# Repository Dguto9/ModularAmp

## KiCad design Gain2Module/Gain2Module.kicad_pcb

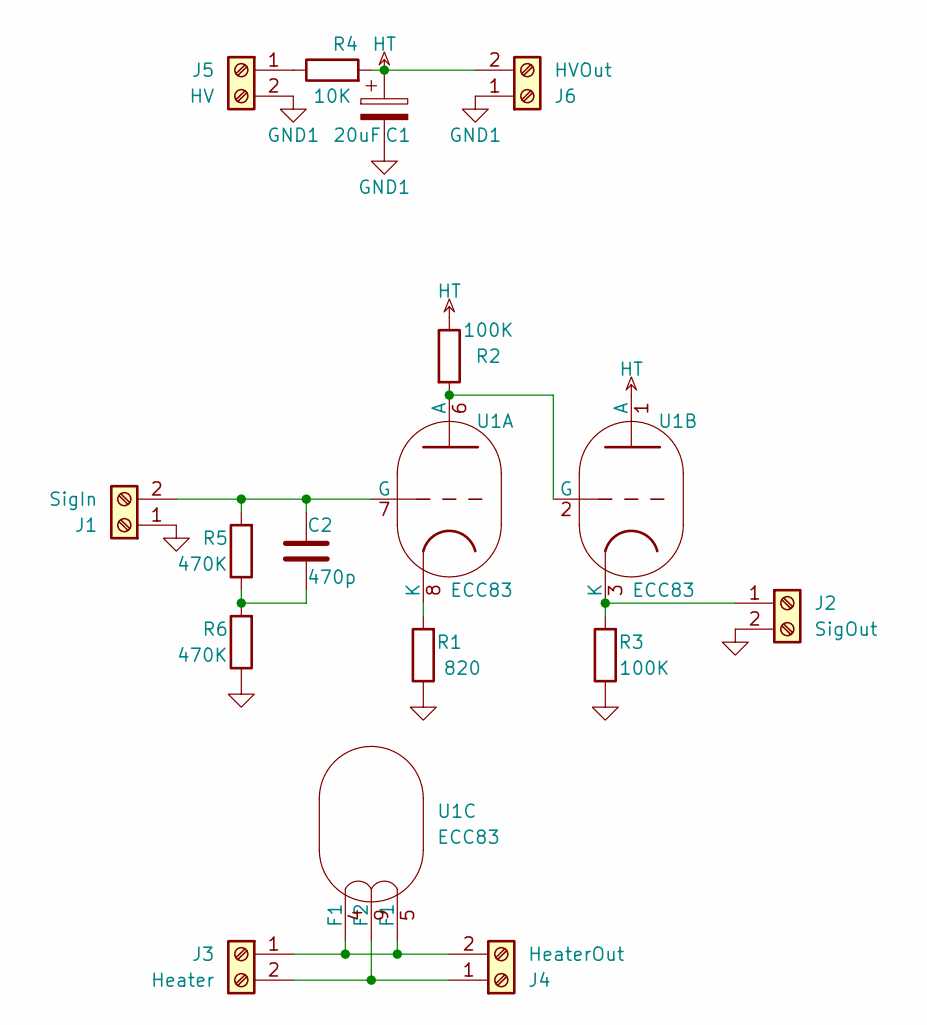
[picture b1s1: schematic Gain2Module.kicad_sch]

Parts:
C1: 20uF; CP_Radial_D13.0mm_P5.00mm
C2: 470p; FG26 Cap
J1: SigIn; Molex_Micro-Fit_3.0_43650-0200_1x02_P3.00mm_Horizontal
J2: SigOut; Molex_Micro-Fit_3.0_43650-0200_1x02_P3.00mm_Horizontal
J3: Heater; Molex_Micro-Fit_3.0_43650-0215_1x02_P3.00mm_Vertical
J4: HeaterOut; Molex_Micro-Fit_3.0_43650-0215_1x02_P3.00mm_Vertical
J5: HV; Molex_Micro-Fit_3.0_43650-0200_1x02_P3.00mm_Horizontal
J6: HVOut; Molex_Micro-Fit_3.0_43650-0200_1x02_P3.00mm_Horizontal
R1: 820; R_Axial_DIN0309_L9.0mm_D3.2mm_P12.70mm_Horizontal
R2, R3: 100K; R_Axial_DIN0309_L9.0mm_D3.2mm_P12.70mm_Horizontal
R4: 10K; R_Axial_DIN0309_L9.0mm_D3.2mm_P12.70mm_Horizontal
R5, R6: 470K; R_Axial_DIN0309_L9.0mm_D3.2mm_P12.70mm_Horizontal
U1: ECC83; BELTON_VT9-PT

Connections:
GND: J1.1, J2.2, R1.1, R3.1, R6.1
GND1: C1.2, J5.2, J6.1
HT: C1.1, J6.2, R2.1, R4.2, U1.1 (A)
unnamed: C2.2, R5.1, R6.2
unnamed: C2.1, J1.2, R5.2, U1.7 (G)
unnamed: J2.1, R3.2, U1.3 (K)
unnamed: J3.1, J4.2, U1.4 (F1), U1.5 (F1)
unnamed: J3.2, J4.1, U1.9 (F2)
unnamed: J5.1, R4.1
unnamed: R2.2, U1.2 (G), U1.6 (A)
unnamed: R1.2, U1.8 (K)

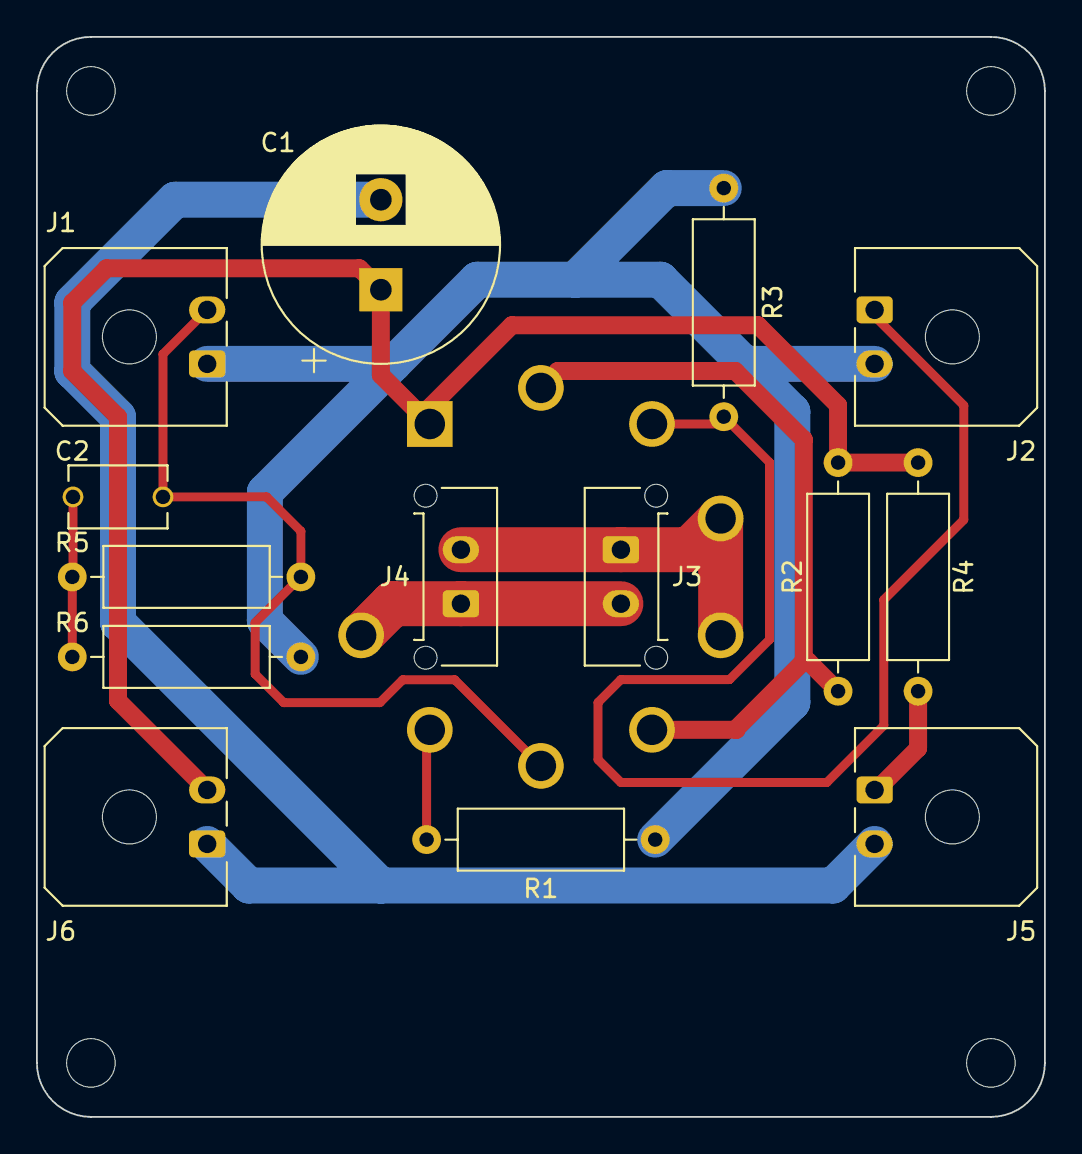
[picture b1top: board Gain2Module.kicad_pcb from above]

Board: 2 copper layers, 56.0 x 60.0 mm, 15 parts (1 on the bottom side), 11 nets.

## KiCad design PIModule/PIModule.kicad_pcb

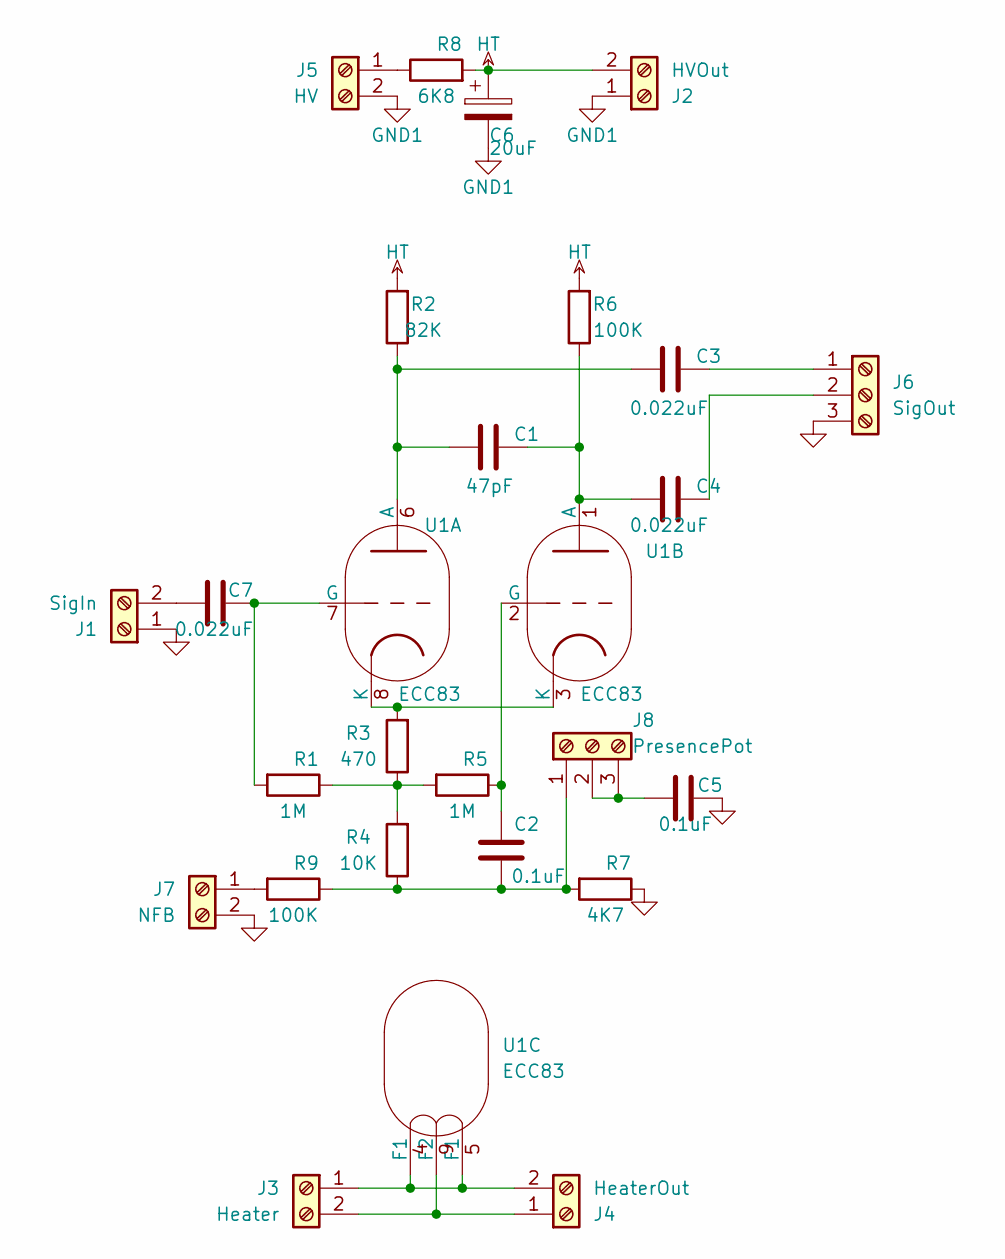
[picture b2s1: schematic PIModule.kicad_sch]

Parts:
C1: 47pF; FG26 Cap
C2, C5: 0.1uF; FG26 Cap
C3, C4, C7: 0.022uF; C_Rect_L13.0mm_W4.0mm_P10.00mm_FKS3_FKP3_MKS4
C6: 20uF; CP_Radial_D13.0mm_P5.00mm
J1: SigIn; Molex_Micro-Fit_3.0_43650-0200_1x02_P3.00mm_Horizontal
J2: HVOut; Molex_Micro-Fit_3.0_43650-0200_1x02_P3.00mm_Horizontal
J3: Heater; Molex_Micro-Fit_3.0_43650-0215_1x02_P3.00mm_Vertical
J4: HeaterOut; Molex_Micro-Fit_3.0_43650-0215_1x02_P3.00mm_Vertical
J5: HV; Molex_Micro-Fit_3.0_43650-0200_1x02_P3.00mm_Horizontal
J6: SigOut; Molex_Micro-Fit_3.0_43650-0300_1x03_P3.00mm_Horizontal
J7: NFB; Molex_Micro-Fit_3.0_43650-0215_1x02_P3.00mm_Vertical
J8: PresencePot; Molex_Micro-Fit_3.0_43650-0315_1x03_P3.00mm_Vertical
R1, R5: 1M; R_Axial_DIN0309_L9.0mm_D3.2mm_P12.70mm_Horizontal
R2: 82K; R_Axial_DIN0309_L9.0mm_D3.2mm_P12.70mm_Horizontal
R3: 470; R_Axial_DIN0309_L9.0mm_D3.2mm_P12.70mm_Horizontal
R4: 10K; R_Axial_DIN0309_L9.0mm_D3.2mm_P12.70mm_Horizontal
R6, R9: 100K; R_Axial_DIN0309_L9.0mm_D3.2mm_P12.70mm_Horizontal
R7: 4K7; R_Axial_DIN0309_L9.0mm_D3.2mm_P12.70mm_Horizontal
R8: 6K8; R_Axial_DIN0309_L9.0mm_D3.2mm_P12.70mm_Horizontal
U1: ECC83; BELTON_VT9-PT

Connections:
GND: C5.1, J1.1, J6.3, J7.2, R7.1
GND1: C6.2, J2.1, J5.2
HT: C6.1, J2.2, R2.2, R6.2, R8.2
unnamed: C7.1, J1.2
unnamed: J3.1, J4.2, U1.4 (F1), U1.5 (F1)
unnamed: J3.2, J4.1, U1.9 (F2)
unnamed: J5.1, R8.1
unnamed: C3.2, J6.1
unnamed: C4.2, J6.2
unnamed: J7.1, R9.2
unnamed: C2.1, J8.1, R4.1, R7.2, R9.1
unnamed: C5.2, J8.2, J8.3
unnamed: R1.1, R3.1, R4.2, R5.2
unnamed: C1.1, C3.1, R2.1, U1.6 (A)
unnamed: C7.2, R1.2, U1.7 (G)
unnamed: R3.2, U1.3 (K), U1.8 (K)
unnamed: C1.2, C4.1, R6.1, U1.1 (A)
unnamed: C2.2, R5.1, U1.2 (G)

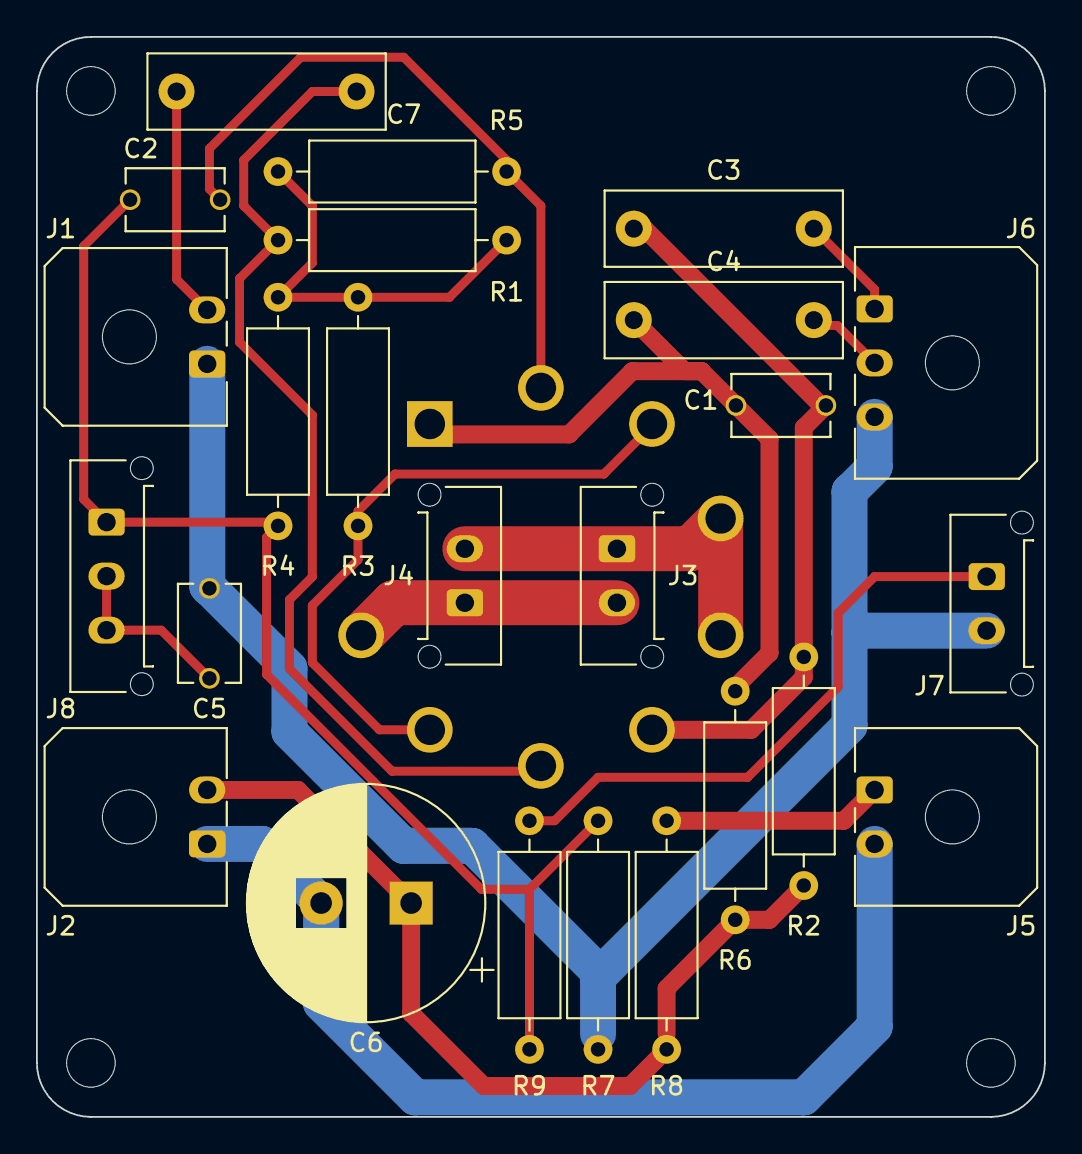
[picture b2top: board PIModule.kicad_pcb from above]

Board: 2 copper layers, 56.0 x 60.0 mm, 25 parts (1 on the bottom side), 18 nets.

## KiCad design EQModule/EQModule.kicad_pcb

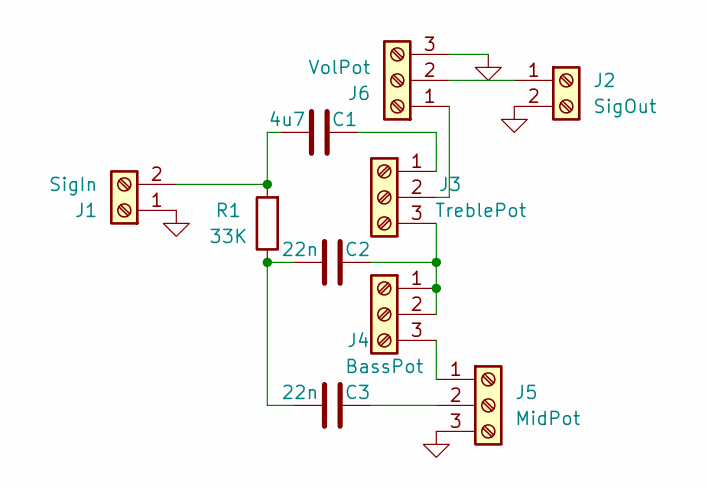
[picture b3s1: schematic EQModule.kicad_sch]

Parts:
C1: 4u7; FG26 Cap
C2, C3: 22n; FG26 Cap
J1: SigIn; Molex_Micro-Fit_3.0_43650-0200_1x02_P3.00mm_Horizontal
J2: SigOut; Molex_Micro-Fit_3.0_43650-0200_1x02_P3.00mm_Horizontal
J3: TreblePot; Molex_Micro-Fit_3.0_43650-0315_1x03_P3.00mm_Vertical
J4: BassPot; Molex_Micro-Fit_3.0_43650-0315_1x03_P3.00mm_Vertical
J5: MidPot; Molex_Micro-Fit_3.0_43650-0315_1x03_P3.00mm_Vertical
J6: VolPot; Molex_Micro-Fit_3.0_43650-0315_1x03_P3.00mm_Vertical
R1: 33K; R_Axial_DIN0309_L9.0mm_D3.2mm_P12.70mm_Horizontal

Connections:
GND: J1.1, J2.2, J5.3, J6.3
unnamed: C2.1, C3.1, R1.1
unnamed: C1.1, J1.2, R1.2
unnamed: J2.1, J6.2
unnamed: C1.2, J3.1
unnamed: J3.2, J6.1
unnamed: C2.2, J3.3, J4.1, J4.2
unnamed: J4.3, J5.1
unnamed: C3.2, J5.2

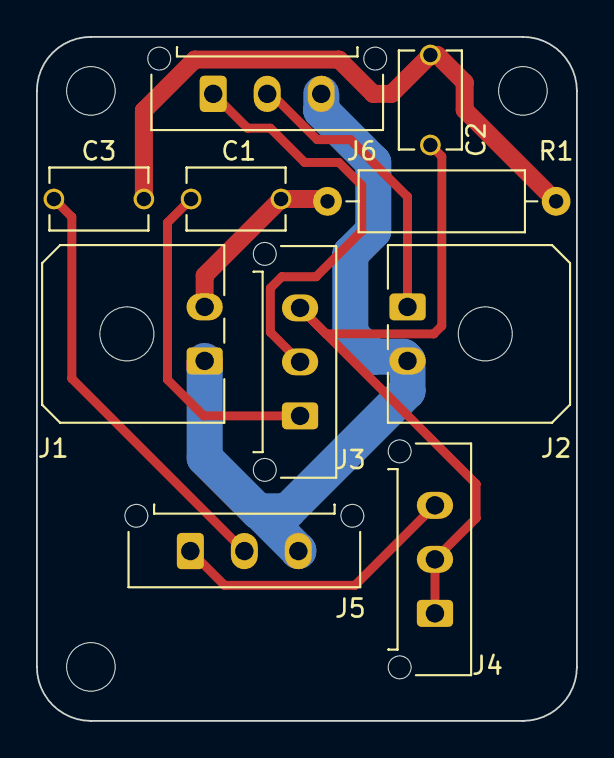
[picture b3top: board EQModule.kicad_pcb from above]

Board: 2 copper layers, 30.0 x 38.0 mm, 10 parts (0 on the bottom side), 9 nets.

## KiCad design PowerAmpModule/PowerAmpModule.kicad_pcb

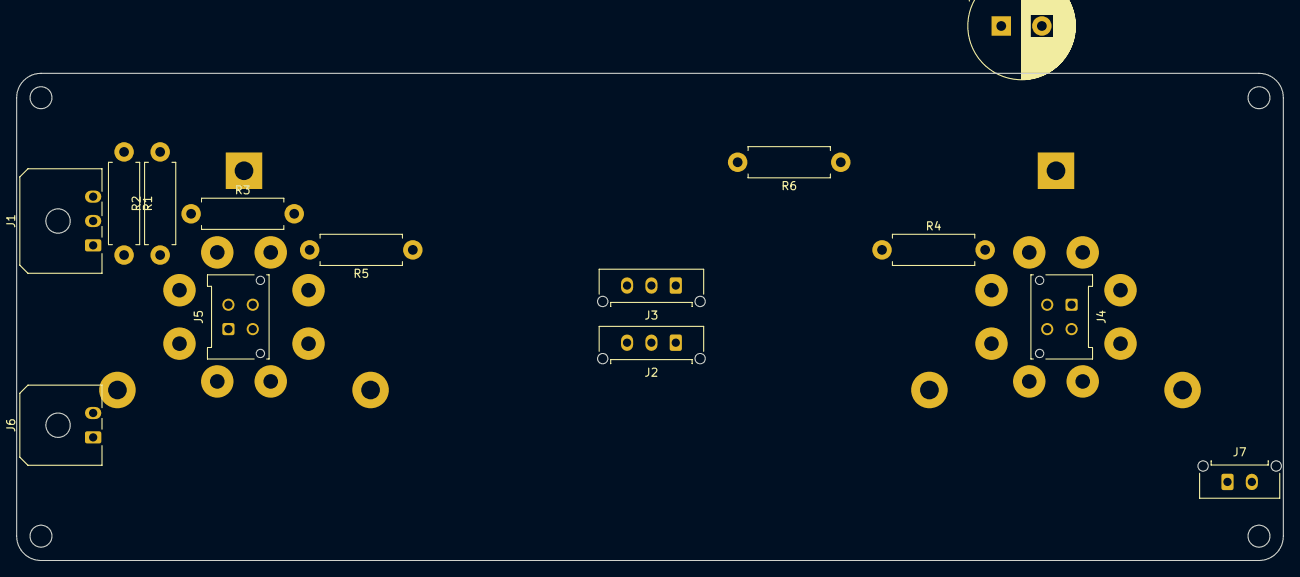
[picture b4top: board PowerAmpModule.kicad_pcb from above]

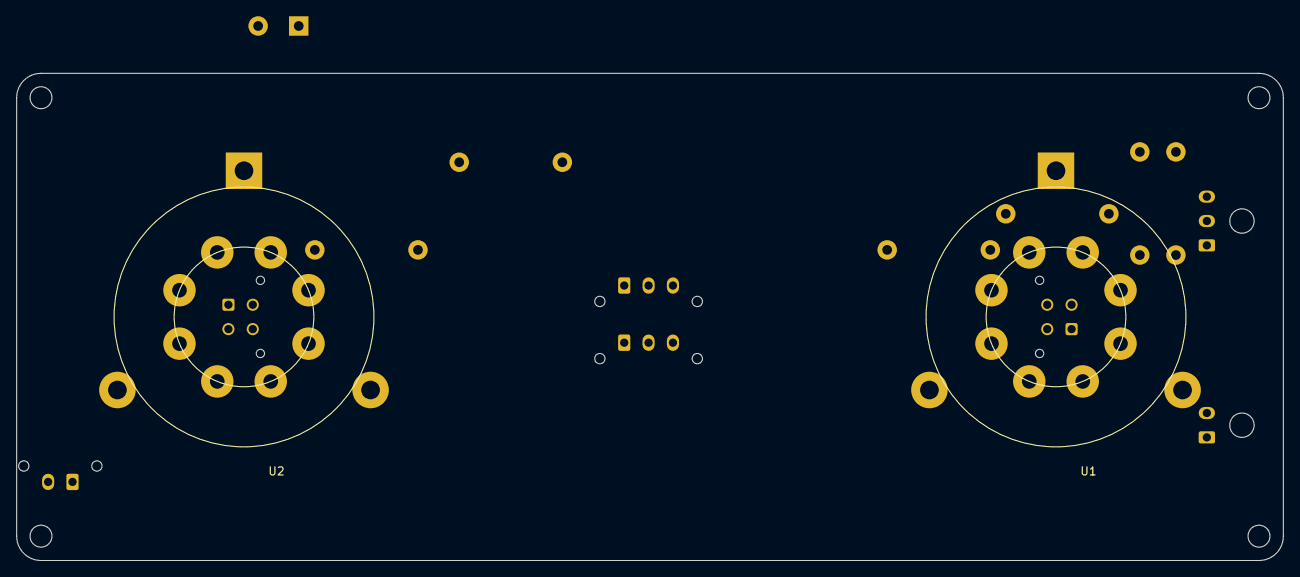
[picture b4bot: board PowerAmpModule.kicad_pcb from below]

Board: 2 copper layers, 156.0 x 60.0 mm, 16 parts (2 on the bottom side), 14 nets, no tracks yet.

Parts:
C1: 20uF; CP_Radial_D13.0mm_P5.00mm
J1: Signal; Molex_Micro-Fit_3.0_43650-0300_1x03_P3.00mm_Horizontal
J2: Power; Molex_Micro-Fit_3.0_43650-0315_1x03_P3.00mm_Vertical
J3: SignalOut; Molex_Micro-Fit_3.0_43650-0315_1x03_P3.00mm_Vertical
J4: Heater; Molex_Micro-Fit_3.0_43045-0412_2x02_P3.00mm_Vertical
J5: HeaterOut; Molex_Micro-Fit_3.0_43045-0412_2x02_P3.00mm_Vertical
J6: PowerOut; Molex_Micro-Fit_3.0_43650-0200_1x02_P3.00mm_Horizontal
J7: Inductor; Molex_Micro-Fit_3.0_43650-0215_1x02_P3.00mm_Vertical
R1, R2: 220K; R_Axial_DIN0411_L9.9mm_D3.6mm_P12.70mm_Horizontal
R3, R4: 5K6; R_Axial_DIN0411_L9.9mm_D3.6mm_P12.70mm_Horizontal
R5, R6: 1K5; R_Axial_DIN0411_L9.9mm_D3.6mm_P12.70mm_Horizontal
U1, U2: 6V6; BELTON_VT8-PTL-01

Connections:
/Bias: J2.2, R1.1, R2.2
GND: C1.2, J1.1, U1.1 (G3), U1.8 (F1), U2.1 (G3), U2.8 (F1)
GND1: J2.3, J6.2
HT: C1.1, J2.1, J3.2, J6.1, J7.1, J7.2, R5.1, R6.1
unnamed: J1.2, R2.1, R4.1
unnamed: J1.3, R1.2, R3.1
unnamed: J3.1, U1.3 (A)
unnamed: J3.3, U2.3 (A)
unnamed: J4.1, J5.1, U1.2 (F1), U2.2 (F1)
unnamed: J4.2, J5.2, U1.7 (F2), U2.7 (F2)
unnamed: R3.2, U1.5 (G1)
unnamed: R5.2, U1.4 (G2)
unnamed: R4.2, U2.5 (G1)
unnamed: R6.2, U2.4 (G2)

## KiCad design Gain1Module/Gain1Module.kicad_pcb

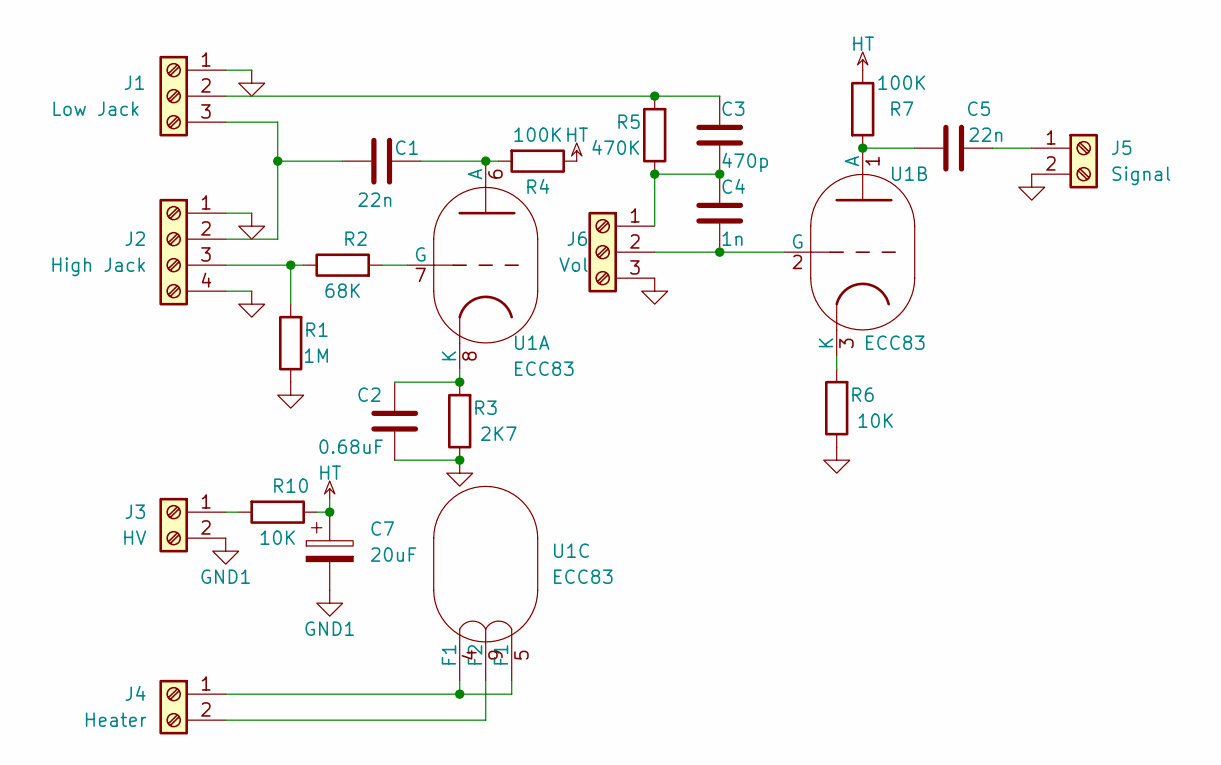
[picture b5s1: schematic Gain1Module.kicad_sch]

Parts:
C1, C5: 22n; C_Rect_L13.0mm_W4.0mm_P10.00mm_FKS3_FKP3_MKS4
C2: 0.68uF; C_Rect_L10.0mm_W4.0mm_P7.50mm_MKS4
C3: 470p; FG26 Cap
C4: 1n; FG26 Cap
C7: 20uF; CP_Radial_D13.0mm_P5.00mm
J1: Low Jack; Molex_Micro-Fit_3.0_43650-0315_1x03_P3.00mm_Vertical
J2: High Jack; Molex_Micro-Fit_3.0_43650-0415_1x04_P3.00mm_Vertical
J3: HV; Molex_Micro-Fit_3.0_43650-0200_1x02_P3.00mm_Horizontal
J4: Heater; Molex_Micro-Fit_3.0_43650-0215_1x02_P3.00mm_Vertical
J5: Signal; Molex_Micro-Fit_3.0_43650-0200_1x02_P3.00mm_Horizontal
J6: Vol; Molex_Micro-Fit_3.0_43650-0315_1x03_P3.00mm_Vertical
R1: 1M; R_Axial_DIN0309_L9.0mm_D3.2mm_P12.70mm_Horizontal
R2: 68K; R_Axial_DIN0309_L9.0mm_D3.2mm_P12.70mm_Horizontal
R3: 2K7; R_Axial_DIN0309_L9.0mm_D3.2mm_P12.70mm_Horizontal
R4, R7: 100K; R_Axial_DIN0411_L9.9mm_D3.6mm_P12.70mm_Horizontal
R5: 470K; R_Axial_DIN0309_L9.0mm_D3.2mm_P12.70mm_Horizontal
R6, R10: 10K; R_Axial_DIN0309_L9.0mm_D3.2mm_P12.70mm_Horizontal
U1: ECC83; BELTON_VT9-PT

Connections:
GND: C2.2, J1.1, J2.1, J2.4, J5.2, J6.3, R1.1, R3.1, R6.1
GND1: C7.2, J3.2
HT: C7.1, R4.1, R7.1, R10.1
unnamed: C3.1, J1.2, R5.2
unnamed: C1.1, J1.3, J2.2
unnamed: J2.3, R1.2, R2.1
unnamed: J3.1, R10.2
unnamed: J4.1, U1.4 (F1), U1.5 (F1)
unnamed: J4.2, U1.9 (F2)
unnamed: C5.2, J5.1
unnamed: C3.2, C4.1, J6.1, R5.1
unnamed: C4.2, J6.2, U1.2 (G)
unnamed: C1.2, R4.2, U1.6 (A)
unnamed: R2.2, U1.7 (G)
unnamed: C2.1, R3.2, U1.8 (K)
unnamed: C5.1, R7.2, U1.1 (A)
unnamed: R6.2, U1.3 (K)

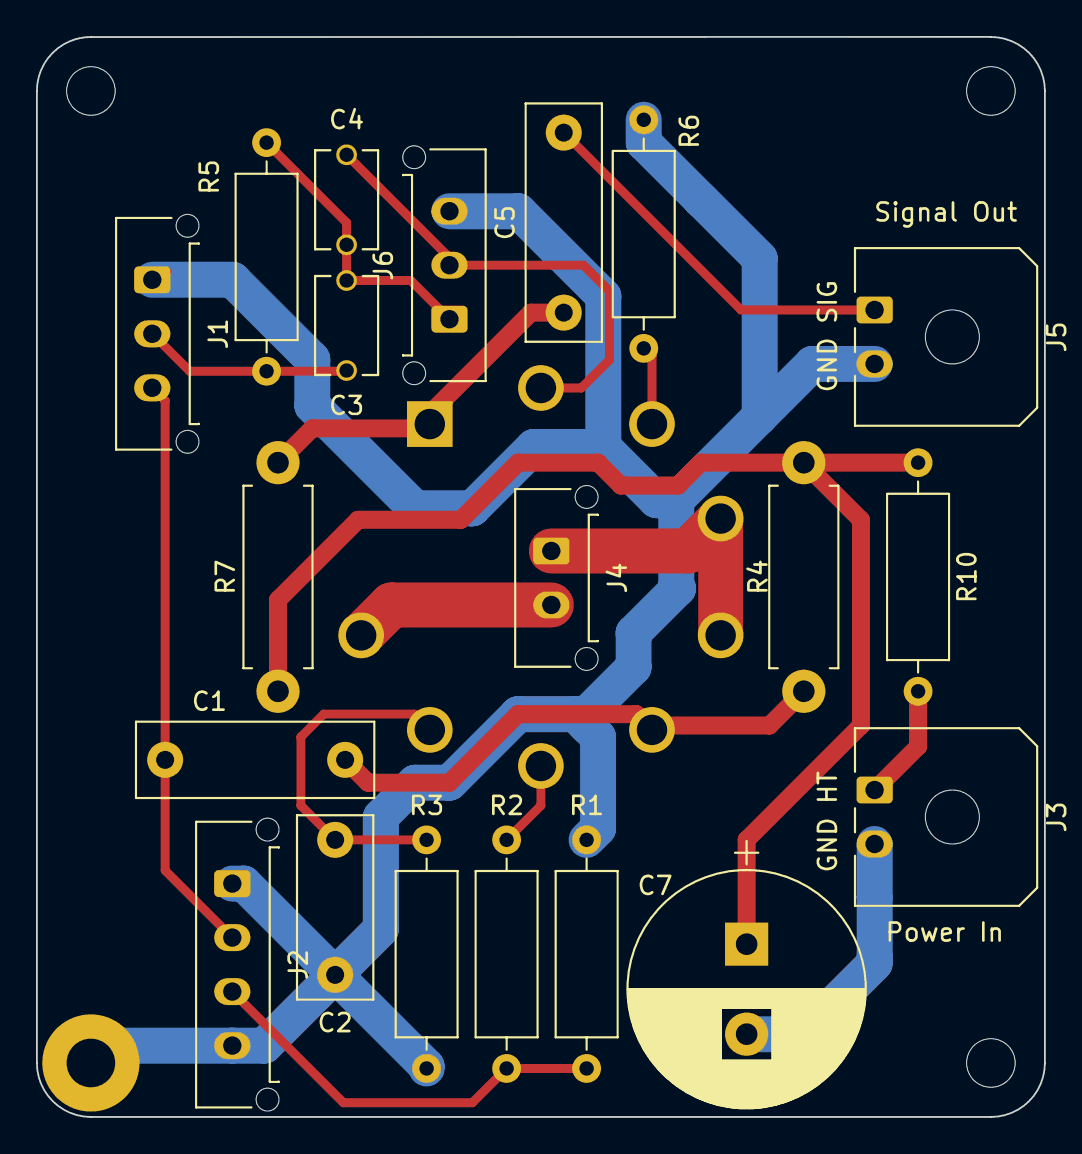
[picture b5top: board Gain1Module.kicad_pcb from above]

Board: 2 copper layers, 56.0 x 60.0 mm, 21 parts (1 on the bottom side), 17 nets.

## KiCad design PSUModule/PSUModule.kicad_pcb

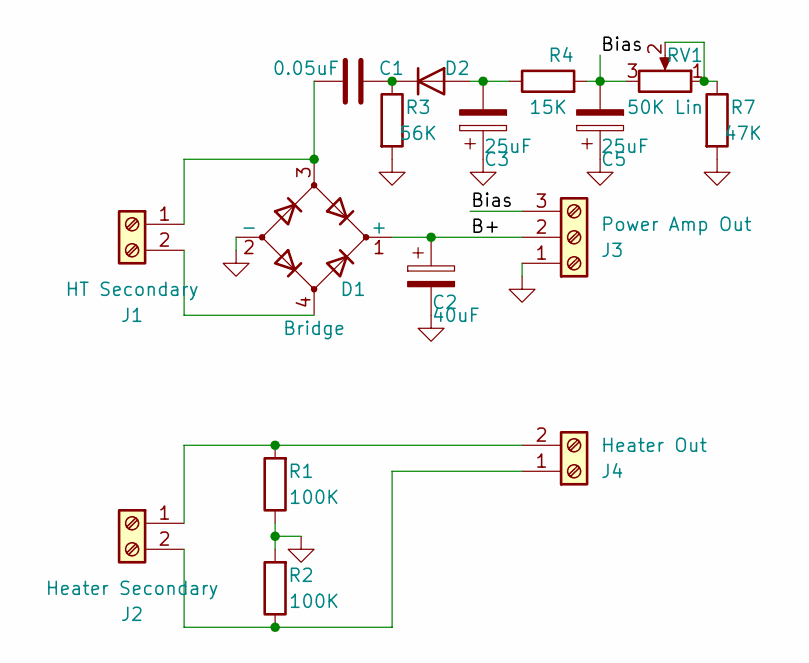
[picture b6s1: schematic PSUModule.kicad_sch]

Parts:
C1: 0.05uF; CAPRR1500W80L1800T700H1250
C2: 40uF; CP_Radial_D13.0mm_P5.00mm
C3, C5: 25uF; CP_Radial_D13.0mm_P5.00mm
D1: Bridge; Diode_Bridge_Vishay_GBL
D2: D; D_DO-41_SOD81_P7.62mm_Horizontal
J1: HT Secondary; Molex_Micro-Fit_3.0_43045-0412_2x02_P3.00mm_Vertical
J2: Heater Secondary; Molex_Micro-Fit_3.0_43045-0412_2x02_P3.00mm_Vertical
J3: Power Amp Out; Molex_Micro-Fit_3.0_43650-0315_1x03_P3.00mm_Vertical
J4: Heater Out; Molex_Micro-Fit_3.0_43650-0215_1x02_P3.00mm_Vertical
R1, R2: 100K; R_Axial_DIN0309_L9.0mm_D3.2mm_P12.70mm_Horizontal
R3: 56K; R_Axial_DIN0309_L9.0mm_D3.2mm_P12.70mm_Horizontal
R4: 15K; R_Axial_DIN0309_L9.0mm_D3.2mm_P12.70mm_Horizontal
R7: 47K; R_Axial_DIN0309_L9.0mm_D3.2mm_P12.70mm_Horizontal
RV1: 50K Lin; TRIM_PV36W503C01B00

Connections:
/B+: C2.1, D1.1 (+), J3.2
/Bias: C5.2, J3.3, R4.2, RV1.3
GND: C2.2, C3.1, C5.1, D1.2 (-), J3.1, R1.1, R2.2, R3.2, R7.2
unnamed: C3.2, D2.2 (A), R4.1
unnamed: C1.2, D2.1 (K), R3.1
unnamed: C1.1, D1.3, J1.1, J1.3
unnamed: D1.4, J1.2, J1.4
unnamed: J2.1, J2.3, J4.2, R1.2
unnamed: J2.2, J2.4, J4.1, R2.1
unnamed: R7.1, RV1.1, RV1.2

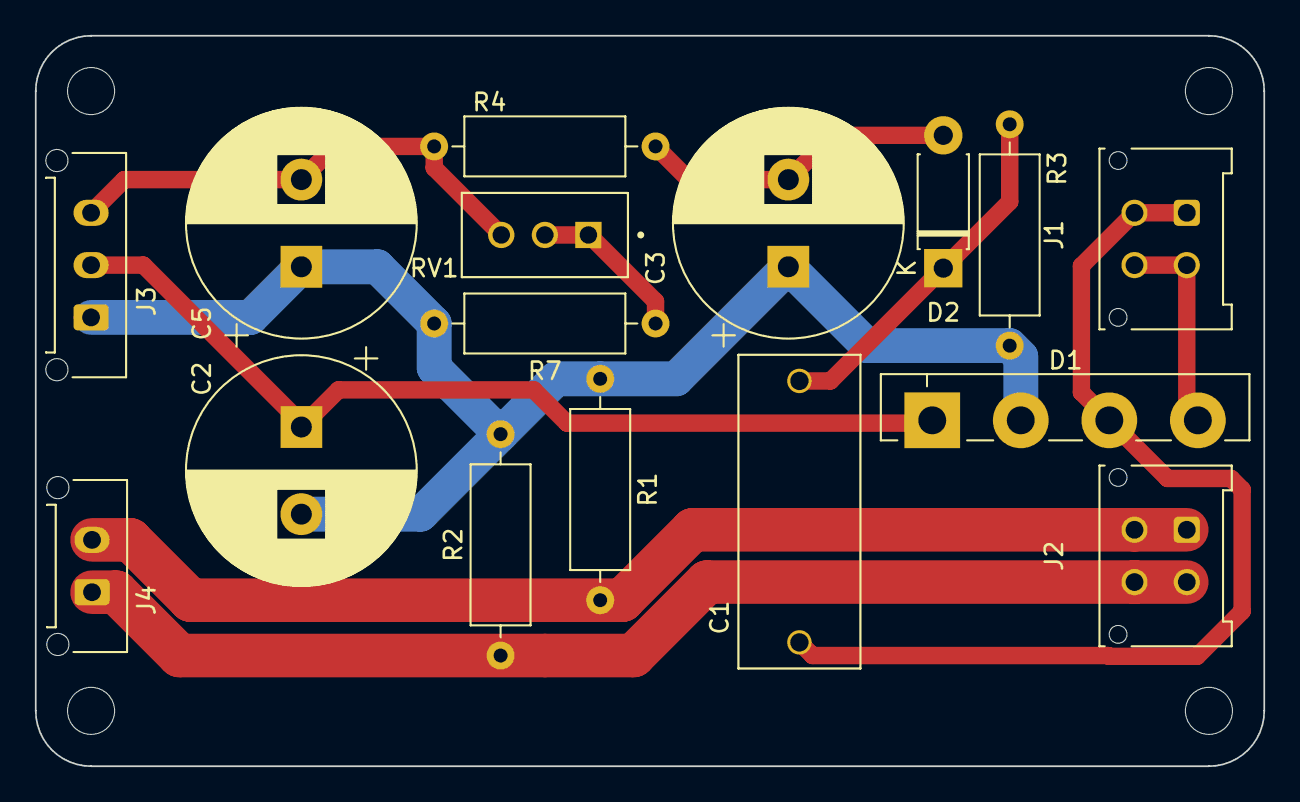
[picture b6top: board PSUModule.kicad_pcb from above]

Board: 2 copper layers, 70.5 x 41.9 mm, 16 parts (0 on the bottom side), 10 nets.

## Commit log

2024-07-12 Add board designs for power supply, gain stage 1 and 2, and phase inverter
2024-07-12 Reroute phase inverter
2024-07-20 Change connector footprints to contain 3D models. Make necessary PCB modifications to address errors found in the design
2024-07-21 Standardized hole size across all boards
